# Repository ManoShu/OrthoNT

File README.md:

# OrthoNT

An open-source, QMK-compatible, (loosely) ABNT2-based 6x14 ortholinear keyboard.

---

Layout:

Links: [KLE](http://www.keyboard-layout-editor.com/#/gists/c8b4991d1be04ef7142aadfa52a7956e), [JSON](https://gist.github.com/ManoShu/c8b4991d1be04ef7142aadfa52a7956e), [QMK](https://github.com/ManoShu/OrthoNT/tree/main/qmk/keyboards/handwired/orthont)

---

## PCB & Plate
The gerber files are under `production`. They had been used and confirmed to work, however use them at your own risk.

## QMK

No plan to integrate to the main QMK repository yet, as I am waiting for a proper VID/PID allocation. The files are on the `qmk` directory; just copy folder to qmk and it should work (HOWEVER the files have been confirmed working on QMK 0.2.2 [check yours with `qmk --version`], previous versions might not have support for some of the tags in the` info.json` file).

## VIA / VIAL

**NOTE: VIA / VIAL files have not been uploaded yet**

A `via` keymap is available allowing to use VIA to change keybindings withou the need to setup QMK. 
It is not integrated with the official repository yet (as I am waiting for a proper VID allocation), but the .json file required to change bindings is available on the `via` directory.

A VIAL-compatible keymap is also available. Drop the keyboard folder to your `vial-qmk` directory and it should also work right off the bat.

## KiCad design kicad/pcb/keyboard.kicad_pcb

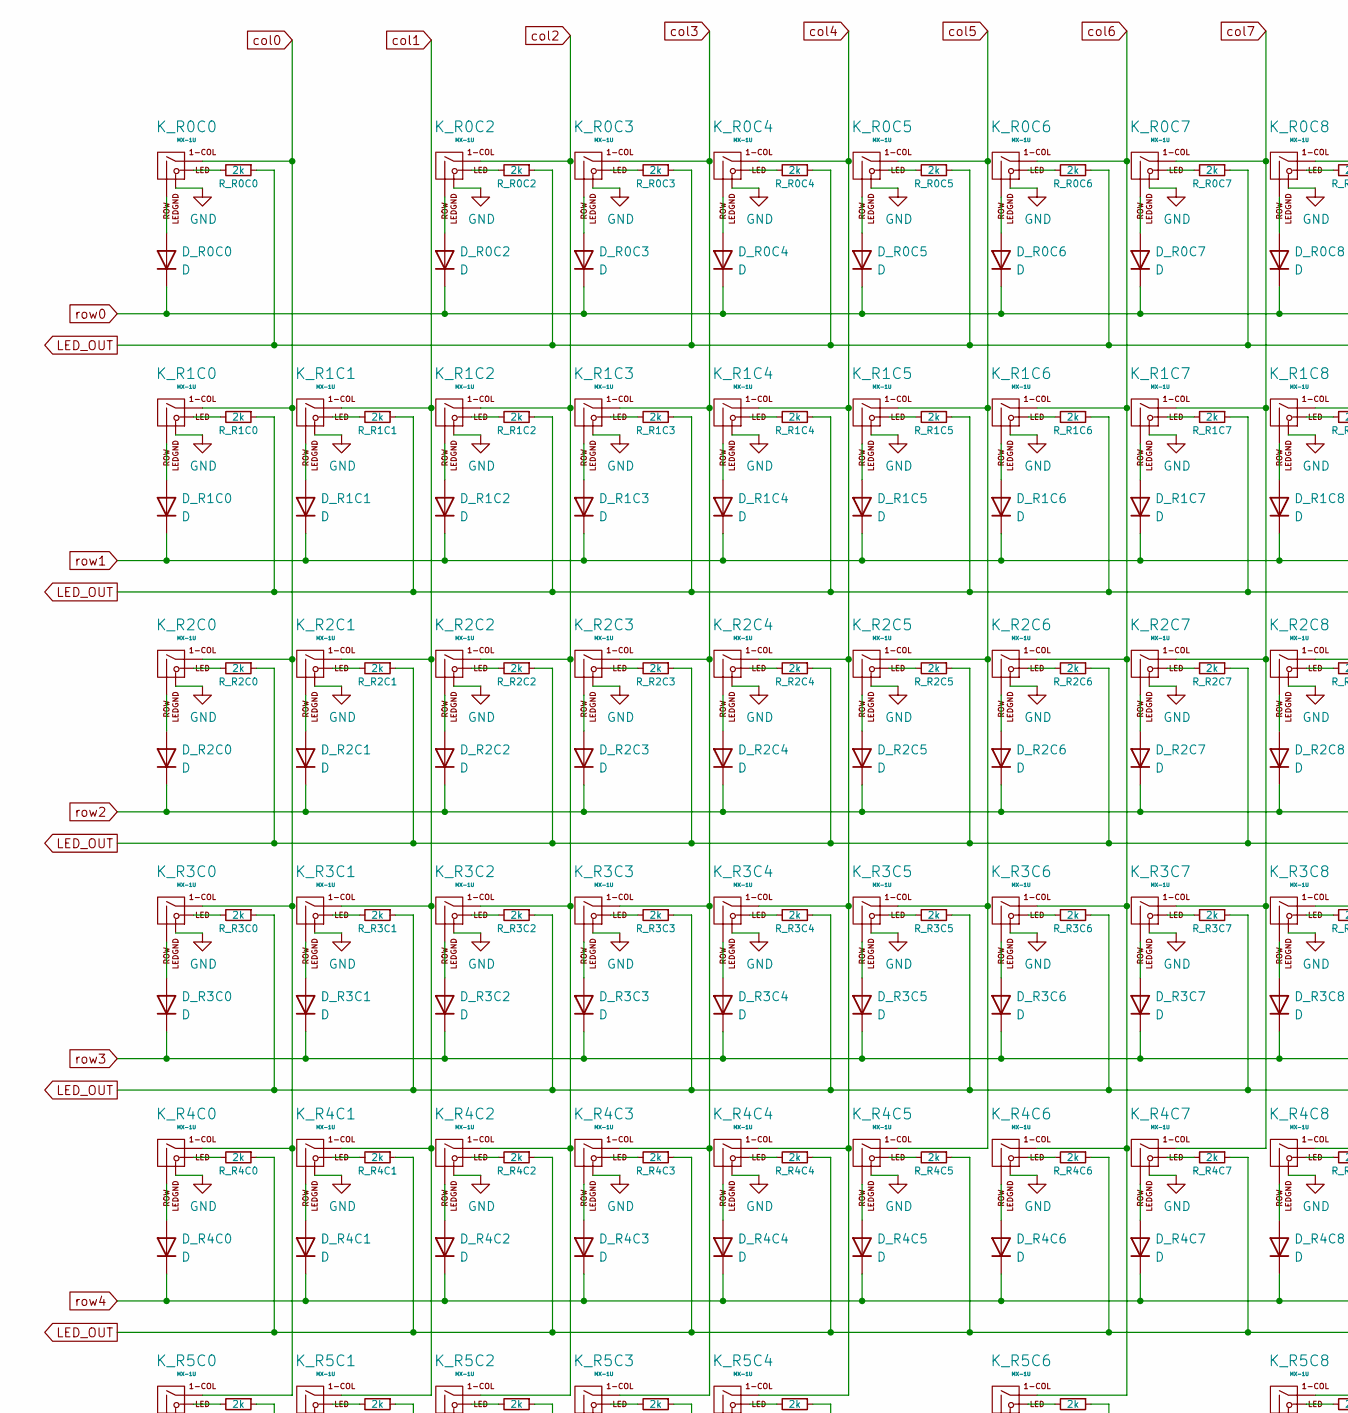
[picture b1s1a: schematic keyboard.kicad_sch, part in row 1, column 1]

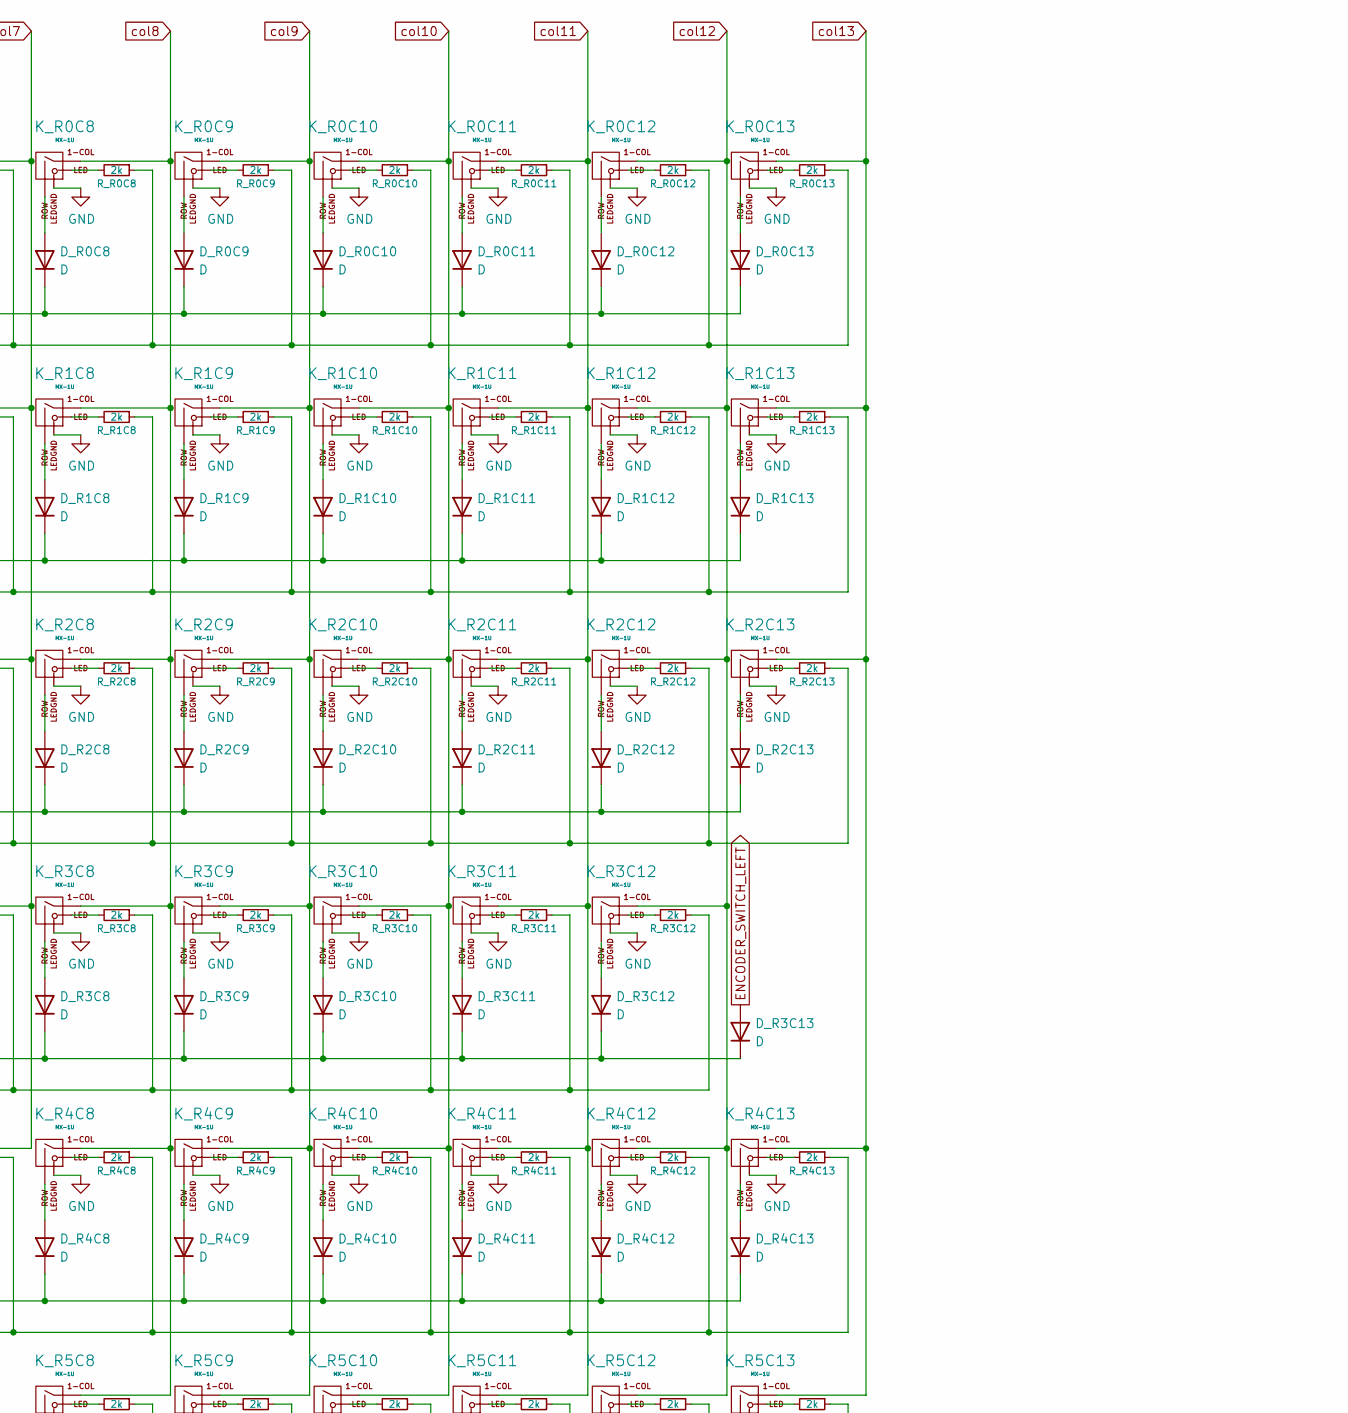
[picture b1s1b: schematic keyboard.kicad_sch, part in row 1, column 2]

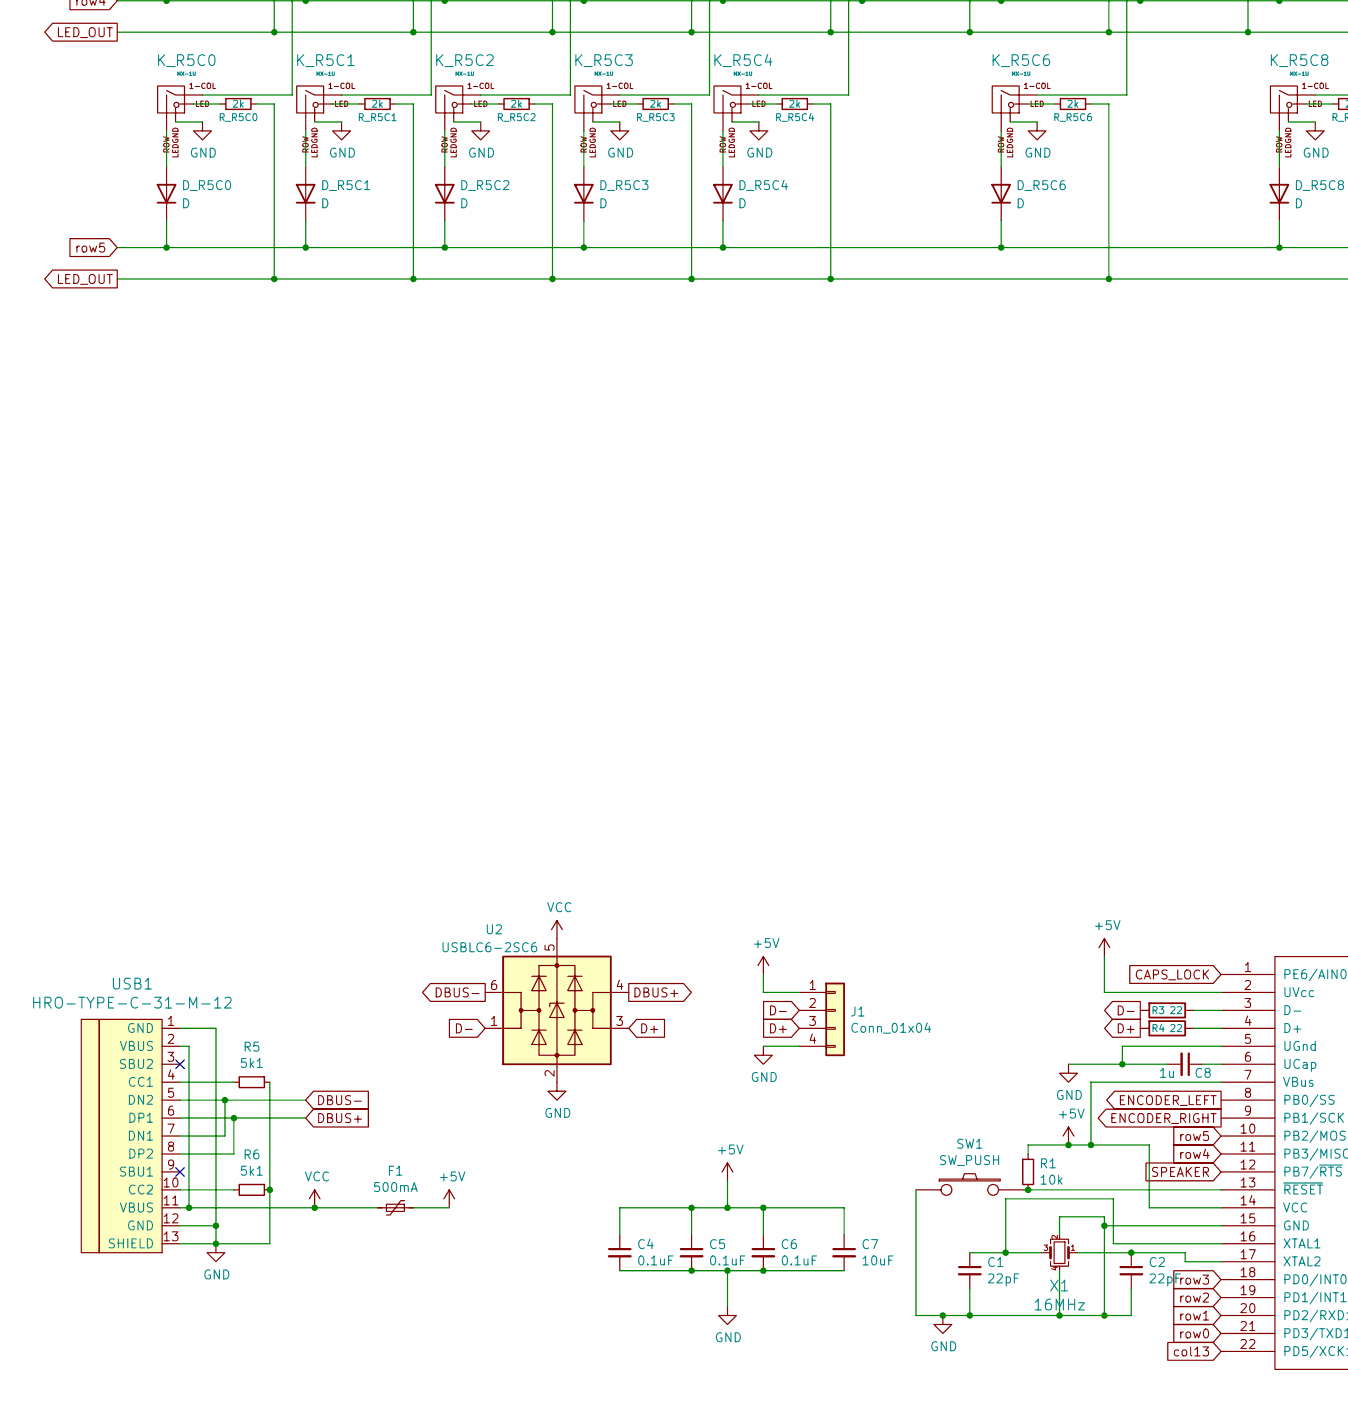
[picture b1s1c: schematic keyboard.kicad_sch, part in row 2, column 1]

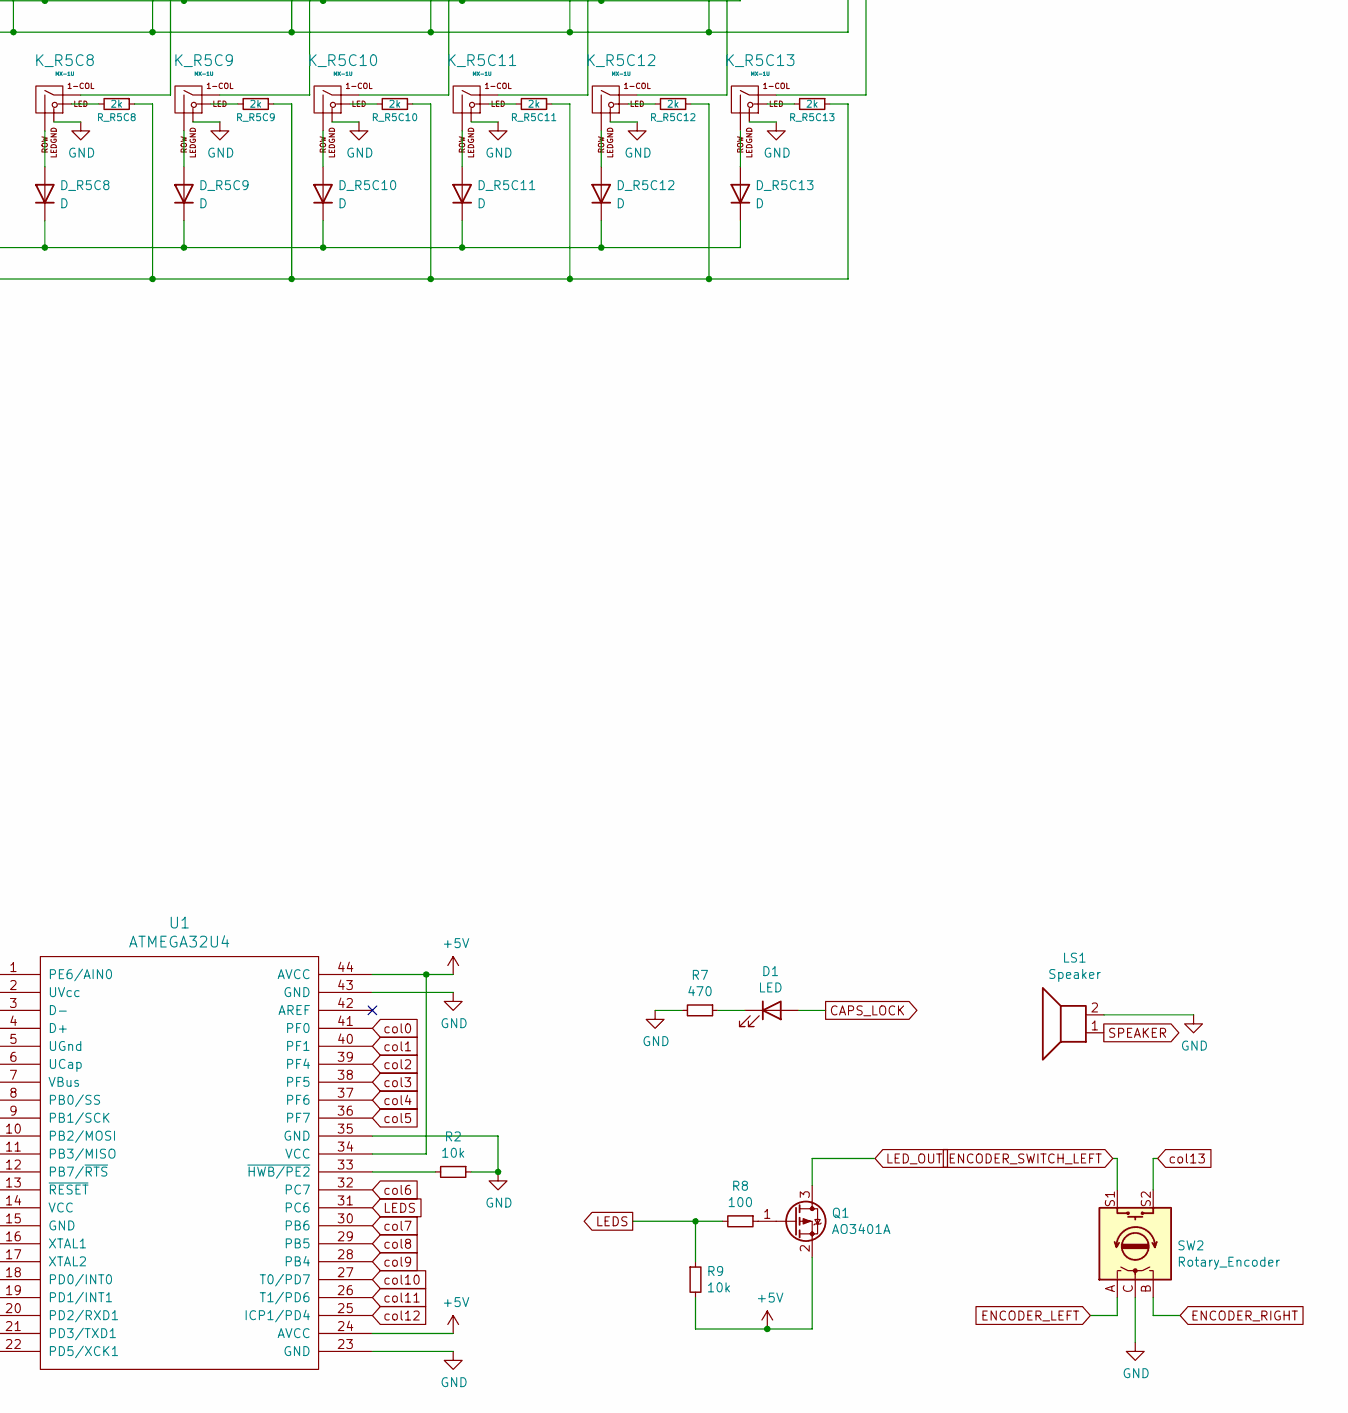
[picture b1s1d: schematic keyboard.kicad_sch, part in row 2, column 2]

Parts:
C1, C2: 22pF; C_0805_2012Metric_Pad1.15x1.40mm_HandSolder
C4, C5, C6: 0.1uF; C_0805_2012Metric_Pad1.15x1.40mm_HandSolder
C7: 10uF; C_0805_2012Metric_Pad1.15x1.40mm_HandSolder
C8: 1u; C_0805_2012Metric_Pad1.15x1.40mm_HandSolder
D1: LED; LED_0603_1608Metric_Pad1.05x0.95mm_HandSolder
D_R0C0, D_R0C2, D_R0C3, D_R0C4, D_R0C5, D_R0C6, D_R0C7, D_R0C8, D_R0C9, D_R0C10, D_R0C11, D_R0C12, D_R0C13, D_R1C0, D_R1C1, D_R1C2, D_R1C3, D_R1C4, D_R1C5, D_R1C6, D_R1C7, D_R1C8, D_R1C9, D_R1C10, D_R1C11, D_R1C12, D_R1C13, D_R2C0, D_R2C1, D_R2C2, D_R2C3, D_R2C4, D_R2C5, D_R2C6, D_R2C7, D_R2C8, D_R2C9, D_R2C10, D_R2C11, D_R2C12, D_R2C13, D_R3C0, D_R3C1, D_R3C2, D_R3C3, D_R3C4, D_R3C5, D_R3C6, D_R3C7, D_R3C8, D_R3C9, D_R3C10, D_R3C11, D_R3C12, D_R3C13, D_R4C0, D_R4C1, D_R4C2, D_R4C3, D_R4C4, D_R4C5, D_R4C6, D_R4C7, D_R4C8, D_R4C9, D_R4C10, D_R4C11, D_R4C12, D_R4C13, D_R5C0, D_R5C1, D_R5C2, D_R5C3, D_R5C4, D_R5C6, D_R5C8, D_R5C9, D_R5C10, D_R5C11, D_R5C12, D_R5C13: D; D_SOD123_hand
F1: 500mA; Fuse_1206_3216Metric_Pad1.42x1.75mm_HandSolder
J1: Conn_01x04; JST_SH_SM04B-SRSS-TB_1x04-1MP_P1.00mm_Horizontal
K_R0C0, K_R0C2, K_R0C3, K_R0C4, K_R0C5, K_R0C6, K_R0C7, K_R0C8, K_R0C9, K_R0C10, K_R0C11, K_R0C12, K_R0C13, K_R1C0, K_R1C1, K_R1C2, K_R1C3, K_R1C4, K_R1C5, K_R1C6, K_R1C7, K_R1C8, K_R1C9, K_R1C10, K_R1C11, K_R1C12, K_R1C13, K_R2C0, K_R2C1, K_R2C2, K_R2C3, K_R2C4, K_R2C5, K_R2C6, K_R2C7, K_R2C8, K_R2C9, K_R2C10, K_R2C11, K_R2C12, K_R3C0, K_R3C1, K_R3C2, K_R3C3, K_R3C4, K_R3C5, K_R3C6, K_R3C7, K_R3C8, K_R3C9, K_R3C10, K_R3C11, K_R3C12, K_R4C0, K_R4C1, K_R4C2, K_R4C3, K_R4C4, K_R4C5, K_R4C6, K_R4C7, K_R4C8, K_R4C9, K_R4C10, K_R4C11, K_R4C12, K_R4C13, K_R5C0, K_R5C1, K_R5C2, K_R5C3, K_R5C6, K_R5C9, K_R5C10, K_R5C11, K_R5C12, K_R5C13: MX-1U; MXOnly-1U
K_R2C13: MX-1U; MXOnly-2U_RightAngle
K_R5C4, K_R5C8: MX-1U; MXOnly-2U
LS1: Speaker; PinHeader_1x02_P2.54mm_Horizontal
Q1: AO3401A; SOT-23_Handsoldering
R1, R2, R9: 10k; R_0805_2012Metric_Pad1.15x1.40mm_HandSolder
R3, R4: 22; R_0805_2012Metric_Pad1.15x1.40mm_HandSolder
R5, R6: 5k1; R_0805_2012Metric_Pad1.15x1.40mm_HandSolder
R7: 470; R_0805_2012Metric_Pad1.15x1.40mm_HandSolder
R8: 100; R_0805_2012Metric_Pad1.15x1.40mm_HandSolder
R_R0C0, R_R0C2, R_R0C3, R_R0C4, R_R0C5, R_R0C6, R_R0C7, R_R0C8, R_R0C9, R_R0C10, R_R0C11, R_R0C12, R_R0C13, R_R1C0, R_R1C1, R_R1C2, R_R1C3, R_R1C4, R_R1C5, R_R1C6, R_R1C7, R_R1C8, R_R1C9, R_R1C10, R_R1C11, R_R1C12, R_R1C13, R_R2C0, R_R2C1, R_R2C2, R_R2C3, R_R2C4, R_R2C5, R_R2C6, R_R2C7, R_R2C8, R_R2C9, R_R2C10, R_R2C11, R_R2C12, R_R2C13, R_R3C0, R_R3C1, R_R3C2, R_R3C3, R_R3C4, R_R3C5, R_R3C6, R_R3C7, R_R3C8, R_R3C9, R_R3C10, R_R3C11, R_R3C12, R_R4C0, R_R4C1, R_R4C2, R_R4C3, R_R4C4, R_R4C5, R_R4C6, R_R4C7, R_R4C8, R_R4C9, R_R4C10, R_R4C11, R_R4C12, R_R4C13, R_R5C0, R_R5C1, R_R5C2, R_R5C3, R_R5C4, R_R5C6, R_R5C8, R_R5C9, R_R5C10, R_R5C11, R_R5C12, R_R5C13: 2k; R_0805_2012Metric_Pad1.15x1.40mm_HandSolder
SW1: SW_PUSH; SW_SPST_SKQG_WithStem
SW2: Rotary_Encoder; RotaryEncoder_Alps_EC11E-Switch_Vertical_H20mm
U1: ATMEGA32U4; TQFP-44_10x10mm_P0.8mm
U2: USBLC6-2SC6; SOT-23-6_Handsoldering
USB1: HRO-TYPE-C-31-M-12; HRO-TYPE-C-31-M-12-HandSoldering
X1: 16MHz; Crystal_SMD_3225-4Pin_3.2x2.5mm_HandSoldering

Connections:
+5V: C4.1, C5.1, C6.1, C7.1, F1.1, J1.1, Q1.2 (S), R1.1, R9.2, U1.2 (UVcc), U1.7 (VBus), U1.14 (VCC), U1.24 (AVCC), U1.34 (VCC), U1.44 (AVCC)
CAPS_LOCK: D1.2 (A), U1.1 (PE6/AIN0)
D+: J1.3, R4.2, U2.3 (I/O2)
D-: J1.2, R3.2, U2.1 (I/O1)
DBUS+: U2.4 (I/O2), USB1.6 (DP1), USB1.8 (DP2)
DBUS-: U2.6 (I/O1), USB1.5 (DN2), USB1.7 (DN1)
ENCODER_LEFT: SW2.A, U1.8 (PB0/SS)
ENCODER_RIGHT: SW2.B, U1.9 (PB1/SCK)
ENCODER_SWITCH_LEFT: D_R3C13.2 (A), SW2.S1
GND: C1.2, C2.2, C4.2, C5.2, C6.2, C7.2, C8.2, J1.4, K_R0C0.4 (LEDGND), K_R0C2.4 (LEDGND), K_R0C3.4 (LEDGND), K_R0C4.4 (LEDGND), K_R0C5.4 (LEDGND), K_R0C6.4 (LEDGND), K_R0C7.4 (LEDGND), K_R0C8.4 (LEDGND), K_R0C9.4 (LEDGND), K_R0C10.4 (LEDGND), K_R0C11.4 (LEDGND), K_R0C12.4 (LEDGND), K_R0C13.4 (LEDGND), K_R1C0.4 (LEDGND), K_R1C1.4 (LEDGND), K_R1C2.4 (LEDGND), K_R1C3.4 (LEDGND), K_R1C4.4 (LEDGND), K_R1C5.4 (LEDGND), K_R1C6.4 (LEDGND), K_R1C7.4 (LEDGND), K_R1C8.4 (LEDGND), K_R1C9.4 (LEDGND), K_R1C10.4 (LEDGND), K_R1C11.4 (LEDGND), K_R1C12.4 (LEDGND), K_R1C13.4 (LEDGND), K_R2C0.4 (LEDGND), K_R2C1.4 (LEDGND), K_R2C2.4 (LEDGND), K_R2C3.4 (LEDGND), K_R2C4.4 (LEDGND), K_R2C5.4 (LEDGND), K_R2C6.4 (LEDGND), K_R2C7.4 (LEDGND), K_R2C8.4 (LEDGND), K_R2C9.4 (LEDGND), K_R2C10.4 (LEDGND), K_R2C11.4 (LEDGND), K_R2C12.4 (LEDGND), K_R2C13.4 (LEDGND), K_R3C0.4 (LEDGND), K_R3C1.4 (LEDGND), K_R3C2.4 (LEDGND), K_R3C3.4 (LEDGND), K_R3C4.4 (LEDGND), K_R3C5.4 (LEDGND), K_R3C6.4 (LEDGND), K_R3C7.4 (LEDGND), K_R3C8.4 (LEDGND), K_R3C9.4 (LEDGND), K_R3C10.4 (LEDGND), K_R3C11.4 (LEDGND), K_R3C12.4 (LEDGND), K_R4C0.4 (LEDGND), K_R4C1.4 (LEDGND), K_R4C2.4 (LEDGND), K_R4C3.4 (LEDGND), K_R4C4.4 (LEDGND), K_R4C5.4 (LEDGND), K_R4C6.4 (LEDGND), K_R4C7.4 (LEDGND), K_R4C8.4 (LEDGND), K_R4C9.4 (LEDGND), K_R4C10.4 (LEDGND), K_R4C11.4 (LEDGND), K_R4C12.4 (LEDGND), K_R4C13.4 (LEDGND), K_R5C0.4 (LEDGND), K_R5C1.4 (LEDGND), K_R5C2.4 (LEDGND), K_R5C3.4 (LEDGND), K_R5C4.4 (LEDGND), K_R5C6.4 (LEDGND), K_R5C8.4 (LEDGND), K_R5C9.4 (LEDGND), K_R5C10.4 (LEDGND), K_R5C11.4 (LEDGND), K_R5C12.4 (LEDGND), K_R5C13.4 (LEDGND), LS1.2, R2.1, R5.1, R6.1, R7.2, SW1.1, SW2.C, U1.5 (UGnd), U1.15 (GND), U1.23 (GND), U1.35 (GND), U1.43 (GND), U2.2 (GND), USB1.1 (GND), USB1.12 (GND), USB1.13 (SHIELD), X1.2, X1.4
LEDS: R8.2, R9.1, U1.31 (PC6)
LED_OUT: Q1.3 (D), R_R0C0.1, R_R0C2.1, R_R0C3.1, R_R0C4.1, R_R0C5.1, R_R0C6.1, R_R0C7.1, R_R0C8.1, R_R0C9.1, R_R0C10.1, R_R0C11.1, R_R0C12.1, R_R0C13.1, R_R1C0.1, R_R1C1.1, R_R1C2.1, R_R1C3.1, R_R1C4.1, R_R1C5.1, R_R1C6.1, R_R1C7.1, R_R1C8.1, R_R1C9.1, R_R1C10.1, R_R1C11.1, R_R1C12.1, R_R1C13.1, R_R2C0.1, R_R2C1.1, R_R2C2.1, R_R2C3.1, R_R2C4.1, R_R2C5.1, R_R2C6.1, R_R2C7.1, R_R2C8.1, R_R2C9.1, R_R2C10.1, R_R2C11.1, R_R2C12.1, R_R2C13.1, R_R3C0.1, R_R3C1.1, R_R3C2.1, R_R3C3.1, R_R3C4.1, R_R3C5.1, R_R3C6.1, R_R3C7.1, R_R3C8.1, R_R3C9.1, R_R3C10.1, R_R3C11.1, R_R3C12.1, R_R4C0.1, R_R4C1.1, R_R4C2.1, R_R4C3.1, R_R4C4.1, R_R4C5.1, R_R4C6.1, R_R4C7.1, R_R4C8.1, R_R4C9.1, R_R4C10.1, R_R4C11.1, R_R4C12.1, R_R4C13.1, R_R5C0.1, R_R5C1.1, R_R5C2.1, R_R5C3.1, R_R5C4.1, R_R5C6.1, R_R5C8.1, R_R5C9.1, R_R5C10.1, R_R5C11.1, R_R5C12.1, R_R5C13.1
unnamed: C1.1, U1.16 (XTAL1), X1.3
unnamed: C2.1, U1.17 (XTAL2), X1.1
unnamed: C8.1, U1.6 (UCap)
unnamed: D1.1 (K), R7.1
unnamed: D_R0C0.2 (A), K_R0C0.2 (ROW)
unnamed: D_R0C2.2 (A), K_R0C2.2 (ROW)
unnamed: D_R0C3.2 (A), K_R0C3.2 (ROW)
unnamed: D_R0C4.2 (A), K_R0C4.2 (ROW)
unnamed: D_R0C5.2 (A), K_R0C5.2 (ROW)
unnamed: D_R0C6.2 (A), K_R0C6.2 (ROW)
unnamed: D_R0C7.2 (A), K_R0C7.2 (ROW)
unnamed: D_R0C8.2 (A), K_R0C8.2 (ROW)
unnamed: D_R0C9.2 (A), K_R0C9.2 (ROW)
unnamed: D_R0C10.2 (A), K_R0C10.2 (ROW)
unnamed: D_R0C11.2 (A), K_R0C11.2 (ROW)
unnamed: D_R0C12.2 (A), K_R0C12.2 (ROW)
unnamed: D_R0C13.2 (A), K_R0C13.2 (ROW)
unnamed: D_R1C0.2 (A), K_R1C0.2 (ROW)
unnamed: D_R1C1.2 (A), K_R1C1.2 (ROW)
unnamed: D_R1C2.2 (A), K_R1C2.2 (ROW)
unnamed: D_R1C3.2 (A), K_R1C3.2 (ROW)
unnamed: D_R1C4.2 (A), K_R1C4.2 (ROW)
unnamed: D_R1C5.2 (A), K_R1C5.2 (ROW)
unnamed: D_R1C6.2 (A), K_R1C6.2 (ROW)
unnamed: D_R1C7.2 (A), K_R1C7.2 (ROW)
unnamed: D_R1C8.2 (A), K_R1C8.2 (ROW)
unnamed: D_R1C9.2 (A), K_R1C9.2 (ROW)
unnamed: D_R1C10.2 (A), K_R1C10.2 (ROW)
unnamed: D_R1C11.2 (A), K_R1C11.2 (ROW)
unnamed: D_R1C12.2 (A), K_R1C12.2 (ROW)
unnamed: D_R1C13.2 (A), K_R1C13.2 (ROW)
unnamed: D_R2C0.2 (A), K_R2C0.2 (ROW)
unnamed: D_R2C1.2 (A), K_R2C1.2 (ROW)
unnamed: D_R2C2.2 (A), K_R2C2.2 (ROW)
unnamed: D_R2C3.2 (A), K_R2C3.2 (ROW)
unnamed: D_R2C4.2 (A), K_R2C4.2 (ROW)
unnamed: D_R2C5.2 (A), K_R2C5.2 (ROW)
unnamed: D_R2C6.2 (A), K_R2C6.2 (ROW)
unnamed: D_R2C7.2 (A), K_R2C7.2 (ROW)
unnamed: D_R2C8.2 (A), K_R2C8.2 (ROW)
unnamed: D_R2C9.2 (A), K_R2C9.2 (ROW)
unnamed: D_R2C10.2 (A), K_R2C10.2 (ROW)
unnamed: D_R2C11.2 (A), K_R2C11.2 (ROW)
unnamed: D_R2C12.2 (A), K_R2C12.2 (ROW)
unnamed: D_R2C13.2 (A), K_R2C13.2 (ROW)
unnamed: D_R3C0.2 (A), K_R3C0.2 (ROW)
unnamed: D_R3C1.2 (A), K_R3C1.2 (ROW)
unnamed: D_R3C2.2 (A), K_R3C2.2 (ROW)
unnamed: D_R3C3.2 (A), K_R3C3.2 (ROW)
unnamed: D_R3C4.2 (A), K_R3C4.2 (ROW)
unnamed: D_R3C5.2 (A), K_R3C5.2 (ROW)
unnamed: D_R3C6.2 (A), K_R3C6.2 (ROW)
unnamed: D_R3C7.2 (A), K_R3C7.2 (ROW)
unnamed: D_R3C8.2 (A), K_R3C8.2 (ROW)
unnamed: D_R3C9.2 (A), K_R3C9.2 (ROW)
unnamed: D_R3C10.2 (A), K_R3C10.2 (ROW)
unnamed: D_R3C11.2 (A), K_R3C11.2 (ROW)
unnamed: D_R3C12.2 (A), K_R3C12.2 (ROW)
unnamed: D_R4C0.2 (A), K_R4C0.2 (ROW)
unnamed: D_R4C1.2 (A), K_R4C1.2 (ROW)
unnamed: D_R4C2.2 (A), K_R4C2.2 (ROW)
unnamed: D_R4C3.2 (A), K_R4C3.2 (ROW)
unnamed: D_R4C4.2 (A), K_R4C4.2 (ROW)
unnamed: D_R4C5.2 (A), K_R4C5.2 (ROW)
unnamed: D_R4C6.2 (A), K_R4C6.2 (ROW)
unnamed: D_R4C7.2 (A), K_R4C7.2 (ROW)
unnamed: D_R4C8.2 (A), K_R4C8.2 (ROW)
unnamed: D_R4C9.2 (A), K_R4C9.2 (ROW)
unnamed: D_R4C10.2 (A), K_R4C10.2 (ROW)
unnamed: D_R4C11.2 (A), K_R4C11.2 (ROW)
unnamed: D_R4C12.2 (A), K_R4C12.2 (ROW)
unnamed: D_R4C13.2 (A), K_R4C13.2 (ROW)
unnamed: D_R5C0.2 (A), K_R5C0.2 (ROW)
unnamed: D_R5C1.2 (A), K_R5C1.2 (ROW)
unnamed: D_R5C2.2 (A), K_R5C2.2 (ROW)
unnamed: D_R5C3.2 (A), K_R5C3.2 (ROW)
unnamed: D_R5C4.2 (A), K_R5C4.2 (ROW)
unnamed: D_R5C6.2 (A), K_R5C6.2 (ROW)
unnamed: D_R5C8.2 (A), K_R5C8.2 (ROW)
unnamed: D_R5C9.2 (A), K_R5C9.2 (ROW)
unnamed: D_R5C10.2 (A), K_R5C10.2 (ROW)
unnamed: D_R5C11.2 (A), K_R5C11.2 (ROW)
unnamed: D_R5C12.2 (A), K_R5C12.2 (ROW)
unnamed: D_R5C13.2 (A), K_R5C13.2 (ROW)
unnamed: K_R0C0.3 (LED), R_R0C0.2
unnamed: K_R0C2.3 (LED), R_R0C2.2
unnamed: K_R0C3.3 (LED), R_R0C3.2
unnamed: K_R0C4.3 (LED), R_R0C4.2
unnamed: K_R0C5.3 (LED), R_R0C5.2
unnamed: K_R0C6.3 (LED), R_R0C6.2
unnamed: K_R0C7.3 (LED), R_R0C7.2
unnamed: K_R0C8.3 (LED), R_R0C8.2
unnamed: K_R0C9.3 (LED), R_R0C9.2
unnamed: K_R0C10.3 (LED), R_R0C10.2
unnamed: K_R0C11.3 (LED), R_R0C11.2
unnamed: K_R0C12.3 (LED), R_R0C12.2
unnamed: K_R0C13.3 (LED), R_R0C13.2
unnamed: K_R1C0.3 (LED), R_R1C0.2
unnamed: K_R1C1.3 (LED), R_R1C1.2
unnamed: K_R1C2.3 (LED), R_R1C2.2
unnamed: K_R1C3.3 (LED), R_R1C3.2
unnamed: K_R1C4.3 (LED), R_R1C4.2
unnamed: K_R1C5.3 (LED), R_R1C5.2
unnamed: K_R1C6.3 (LED), R_R1C6.2
unnamed: K_R1C7.3 (LED), R_R1C7.2
unnamed: K_R1C8.3 (LED), R_R1C8.2
unnamed: K_R1C9.3 (LED), R_R1C9.2
unnamed: K_R1C10.3 (LED), R_R1C10.2
unnamed: K_R1C11.3 (LED), R_R1C11.2
unnamed: K_R1C12.3 (LED), R_R1C12.2
unnamed: K_R1C13.3 (LED), R_R1C13.2
unnamed: K_R2C0.3 (LED), R_R2C0.2
unnamed: K_R2C1.3 (LED), R_R2C1.2
unnamed: K_R2C2.3 (LED), R_R2C2.2
unnamed: K_R2C3.3 (LED), R_R2C3.2
unnamed: K_R2C4.3 (LED), R_R2C4.2
unnamed: K_R2C5.3 (LED), R_R2C5.2
unnamed: K_R2C6.3 (LED), R_R2C6.2
unnamed: K_R2C7.3 (LED), R_R2C7.2
unnamed: K_R2C8.3 (LED), R_R2C8.2
unnamed: K_R2C9.3 (LED), R_R2C9.2
unnamed: K_R2C10.3 (LED), R_R2C10.2
unnamed: K_R2C11.3 (LED), R_R2C11.2
unnamed: K_R2C12.3 (LED), R_R2C12.2
unnamed: K_R2C13.3 (LED), R_R2C13.2
unnamed: K_R3C0.3 (LED), R_R3C0.2
unnamed: K_R3C1.3 (LED), R_R3C1.2
unnamed: K_R3C2.3 (LED), R_R3C2.2
unnamed: K_R3C3.3 (LED), R_R3C3.2
unnamed: K_R3C4.3 (LED), R_R3C4.2
unnamed: K_R3C5.3 (LED), R_R3C5.2
unnamed: K_R3C6.3 (LED), R_R3C6.2
unnamed: K_R3C7.3 (LED), R_R3C7.2
unnamed: K_R3C8.3 (LED), R_R3C8.2
unnamed: K_R3C9.3 (LED), R_R3C9.2
unnamed: K_R3C10.3 (LED), R_R3C10.2
unnamed: K_R3C11.3 (LED), R_R3C11.2
unnamed: K_R3C12.3 (LED), R_R3C12.2
unnamed: K_R4C0.3 (LED), R_R4C0.2
unnamed: K_R4C1.3 (LED), R_R4C1.2
unnamed: K_R4C2.3 (LED), R_R4C2.2
unnamed: K_R4C3.3 (LED), R_R4C3.2
unnamed: K_R4C4.3 (LED), R_R4C4.2
unnamed: K_R4C5.3 (LED), R_R4C5.2
unnamed: K_R4C6.3 (LED), R_R4C6.2
unnamed: K_R4C7.3 (LED), R_R4C7.2
unnamed: K_R4C8.3 (LED), R_R4C8.2
unnamed: K_R4C9.3 (LED), R_R4C9.2
unnamed: K_R4C10.3 (LED), R_R4C10.2
unnamed: K_R4C11.3 (LED), R_R4C11.2
unnamed: K_R4C12.3 (LED), R_R4C12.2
unnamed: K_R4C13.3 (LED), R_R4C13.2
unnamed: K_R5C0.3 (LED), R_R5C0.2
unnamed: K_R5C1.3 (LED), R_R5C1.2
unnamed: K_R5C2.3 (LED), R_R5C2.2
unnamed: K_R5C3.3 (LED), R_R5C3.2
unnamed: K_R5C4.3 (LED), R_R5C4.2
unnamed: K_R5C6.3 (LED), R_R5C6.2
unnamed: K_R5C8.3 (LED), R_R5C8.2
unnamed: K_R5C9.3 (LED), R_R5C9.2
unnamed: K_R5C10.3 (LED), R_R5C10.2
unnamed: K_R5C11.3 (LED), R_R5C11.2
unnamed: K_R5C12.3 (LED), R_R5C12.2
unnamed: K_R5C13.3 (LED), R_R5C13.2
unnamed: Q1.1 (G), R8.1
unnamed: R1.2, SW1.2, U1.13 (~RESET)
unnamed: R2.2, U1.33 (~HWB/PE2)
unnamed: R3.1, U1.3 (D-)
unnamed: R4.1, U1.4 (D+)
unnamed: R5.2, USB1.4 (CC1)
unnamed: R6.2, USB1.10 (CC2)
SPEAKER: LS1.1, U1.12 (PB7/~RTS)
VCC: F1.2, U2.5 (VBUS), USB1.2 (VBUS), USB1.11 (VBUS)
col0: K_R0C0.1 (COL), K_R1C0.1 (COL), K_R2C0.1 (COL), K_R3C0.1 (COL), K_R4C0.1 (COL), K_R5C0.1 (COL), U1.41 (PF0)
col1: K_R1C1.1 (COL), K_R2C1.1 (COL), K_R3C1.1 (COL), K_R4C1.1 (COL), K_R5C1.1 (COL), U1.40 (PF1)
col2: K_R0C2.1 (COL), K_R1C2.1 (COL), K_R2C2.1 (COL), K_R3C2.1 (COL), K_R4C2.1 (COL), K_R5C2.1 (COL), U1.39 (PF4)
col3: K_R0C3.1 (COL), K_R1C3.1 (COL), K_R2C3.1 (COL), K_R3C3.1 (COL), K_R4C3.1 (COL), K_R5C3.1 (COL), U1.38 (PF5)
col4: K_R0C4.1 (COL), K_R1C4.1 (COL), K_R2C4.1 (COL), K_R3C4.1 (COL), K_R4C4.1 (COL), K_R5C4.1 (COL), U1.37 (PF6)
col5: K_R0C5.1 (COL), K_R1C5.1 (COL), K_R2C5.1 (COL), K_R3C5.1 (COL), K_R4C5.1 (COL), U1.36 (PF7)
col6: K_R0C6.1 (COL), K_R1C6.1 (COL), K_R2C6.1 (COL), K_R3C6.1 (COL), K_R4C6.1 (COL), K_R5C6.1 (COL), U1.32 (PC7)
col7: K_R0C7.1 (COL), K_R1C7.1 (COL), K_R2C7.1 (COL), K_R3C7.1 (COL), K_R4C7.1 (COL), U1.30 (PB6)
col8: K_R0C8.1 (COL), K_R1C8.1 (COL), K_R2C8.1 (COL), K_R3C8.1 (COL), K_R4C8.1 (COL), K_R5C8.1 (COL), U1.29 (PB5)
col9: K_R0C9.1 (COL), K_R1C9.1 (COL), K_R2C9.1 (COL), K_R3C9.1 (COL), K_R4C9.1 (COL), K_R5C9.1 (COL), U1.28 (PB4)
col10: K_R0C10.1 (COL), K_R1C10.1 (COL), K_R2C10.1 (COL), K_R3C10.1 (COL), K_R4C10.1 (COL), K_R5C10.1 (COL), U1.27 (T0/PD7)
col11: K_R0C11.1 (COL), K_R1C11.1 (COL), K_R2C11.1 (COL), K_R3C11.1 (COL), K_R4C11.1 (COL), K_R5C11.1 (COL), U1.26 (T1/PD6)
col12: K_R0C12.1 (COL), K_R1C12.1 (COL), K_R2C12.1 (COL), K_R3C12.1 (COL), K_R4C12.1 (COL), K_R5C12.1 (COL), U1.25 (ICP1/PD4)
col13: K_R0C13.1 (COL), K_R1C13.1 (COL), K_R2C13.1 (COL), K_R4C13.1 (COL), K_R5C13.1 (COL), SW2.S2, U1.22 (PD5/XCK1)
row0: D_R0C0.1 (K), D_R0C2.1 (K), D_R0C3.1 (K), D_R0C4.1 (K), D_R0C5.1 (K), D_R0C6.1 (K), D_R0C7.1 (K), D_R0C8.1 (K), D_R0C9.1 (K), D_R0C10.1 (K), D_R0C11.1 (K), D_R0C12.1 (K), D_R0C13.1 (K), U1.21 (PD3/TXD1)
row1: D_R1C0.1 (K), D_R1C1.1 (K), D_R1C2.1 (K), D_R1C3.1 (K), D_R1C4.1 (K), D_R1C5.1 (K), D_R1C6.1 (K), D_R1C7.1 (K), D_R1C8.1 (K), D_R1C9.1 (K), D_R1C10.1 (K), D_R1C11.1 (K), D_R1C12.1 (K), D_R1C13.1 (K), U1.20 (PD2/RXD1)
row2: D_R2C0.1 (K), D_R2C1.1 (K), D_R2C2.1 (K), D_R2C3.1 (K), D_R2C4.1 (K), D_R2C5.1 (K), D_R2C6.1 (K), D_R2C7.1 (K), D_R2C8.1 (K), D_R2C9.1 (K), D_R2C10.1 (K), D_R2C11.1 (K), D_R2C12.1 (K), D_R2C13.1 (K), U1.19 (PD1/INT1)
row3: D_R3C0.1 (K), D_R3C1.1 (K), D_R3C2.1 (K), D_R3C3.1 (K), D_R3C4.1 (K), D_R3C5.1 (K), D_R3C6.1 (K), D_R3C7.1 (K), D_R3C8.1 (K), D_R3C9.1 (K), D_R3C10.1 (K), D_R3C11.1 (K), D_R3C12.1 (K), D_R3C13.1 (K), U1.18 (PD0/INT0)
row4: D_R4C0.1 (K), D_R4C1.1 (K), D_R4C2.1 (K), D_R4C3.1 (K), D_R4C4.1 (K), D_R4C5.1 (K), D_R4C6.1 (K), D_R4C7.1 (K), D_R4C8.1 (K), D_R4C9.1 (K), D_R4C10.1 (K), D_R4C11.1 (K), D_R4C12.1 (K), D_R4C13.1 (K), U1.11 (PB3/MISO)
row5: D_R5C0.1 (K), D_R5C1.1 (K), D_R5C2.1 (K), D_R5C3.1 (K), D_R5C4.1 (K), D_R5C6.1 (K), D_R5C8.1 (K), D_R5C9.1 (K), D_R5C10.1 (K), D_R5C11.1 (K), D_R5C12.1 (K), D_R5C13.1 (K), U1.10 (PB2/MOSI)

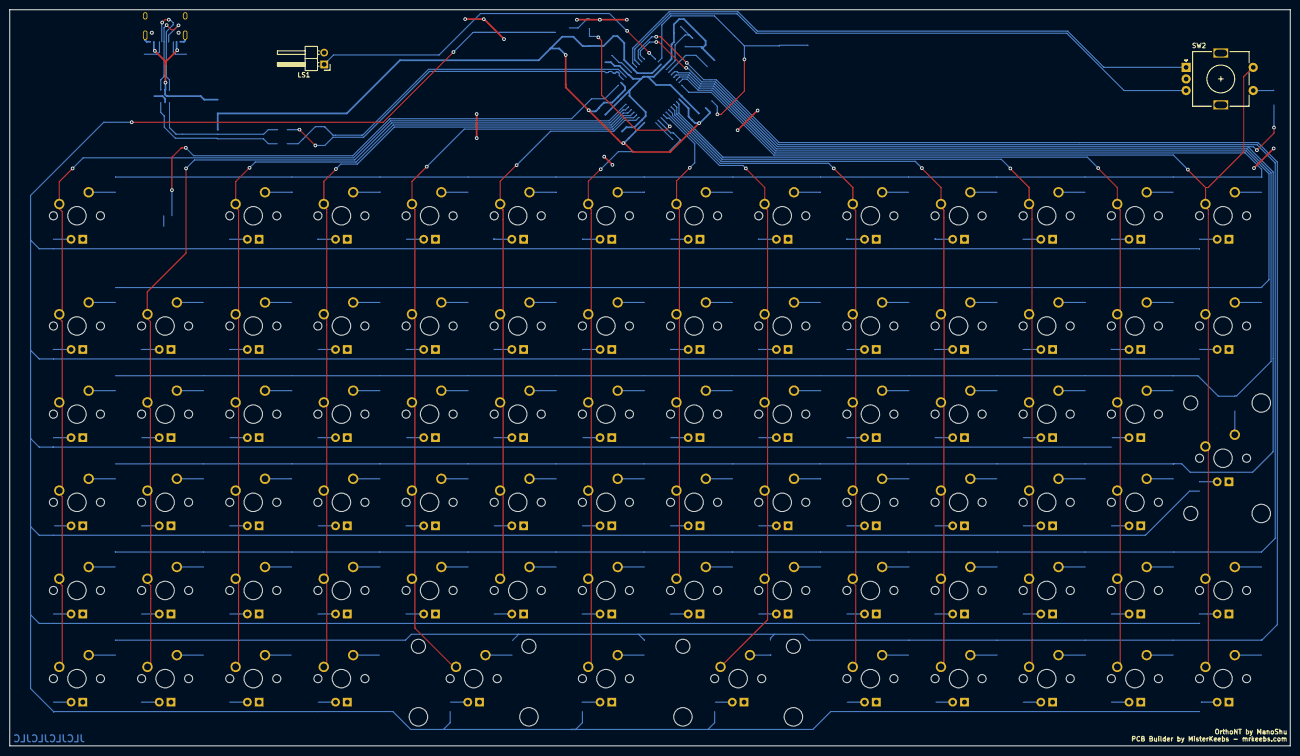
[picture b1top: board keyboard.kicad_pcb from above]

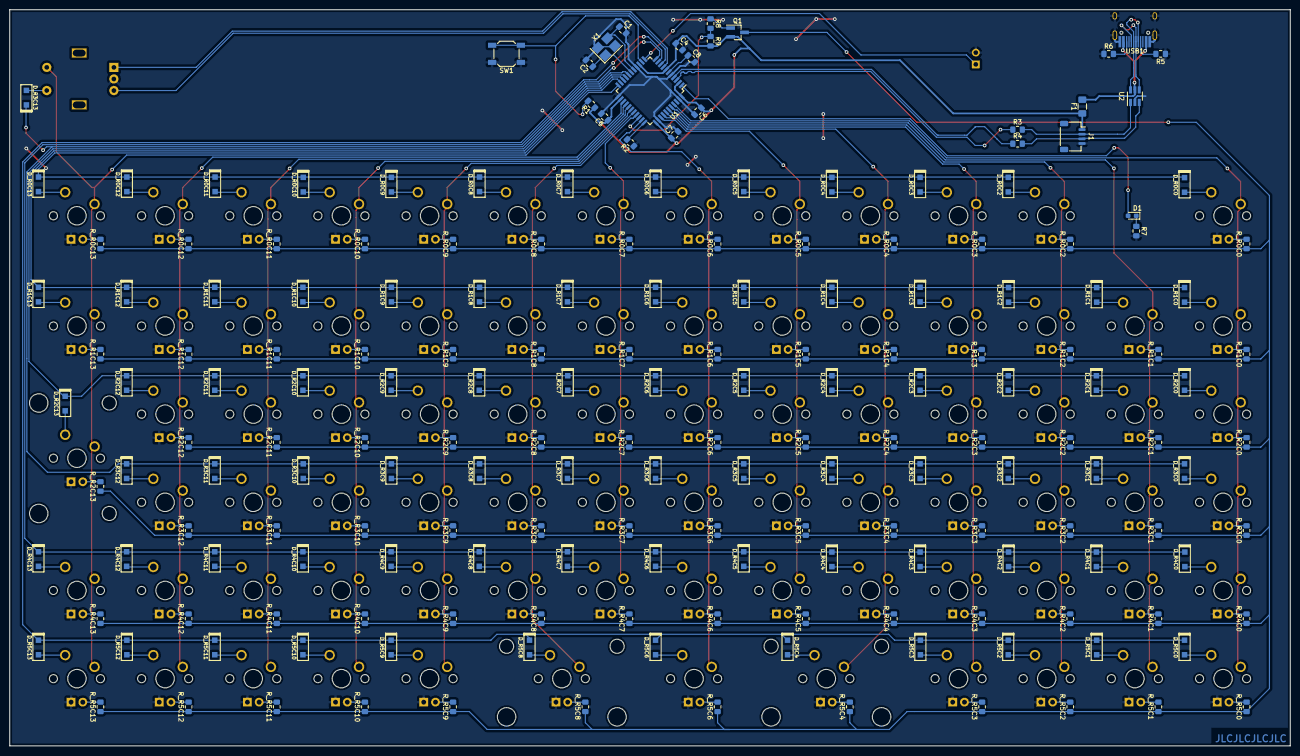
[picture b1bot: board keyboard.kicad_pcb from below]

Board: 2 copper layers, 276.7 x 159.1 mm, 268 parts (186 on the bottom side), 205 nets.

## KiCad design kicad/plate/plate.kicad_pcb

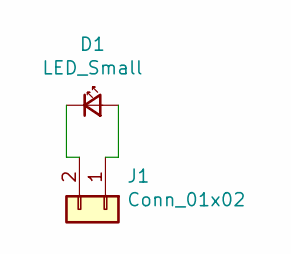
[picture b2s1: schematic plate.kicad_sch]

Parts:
D1: LED_Small; LED_1206_3216Metric_ReverseMount_Hole1.8x2.4mm
J1: Conn_01x02; LED_2816_7142Metric_Pad3.20x4.45mm_HandSolder

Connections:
unnamed: D1.1 (K), J1.2
unnamed: D1.2 (A), J1.1

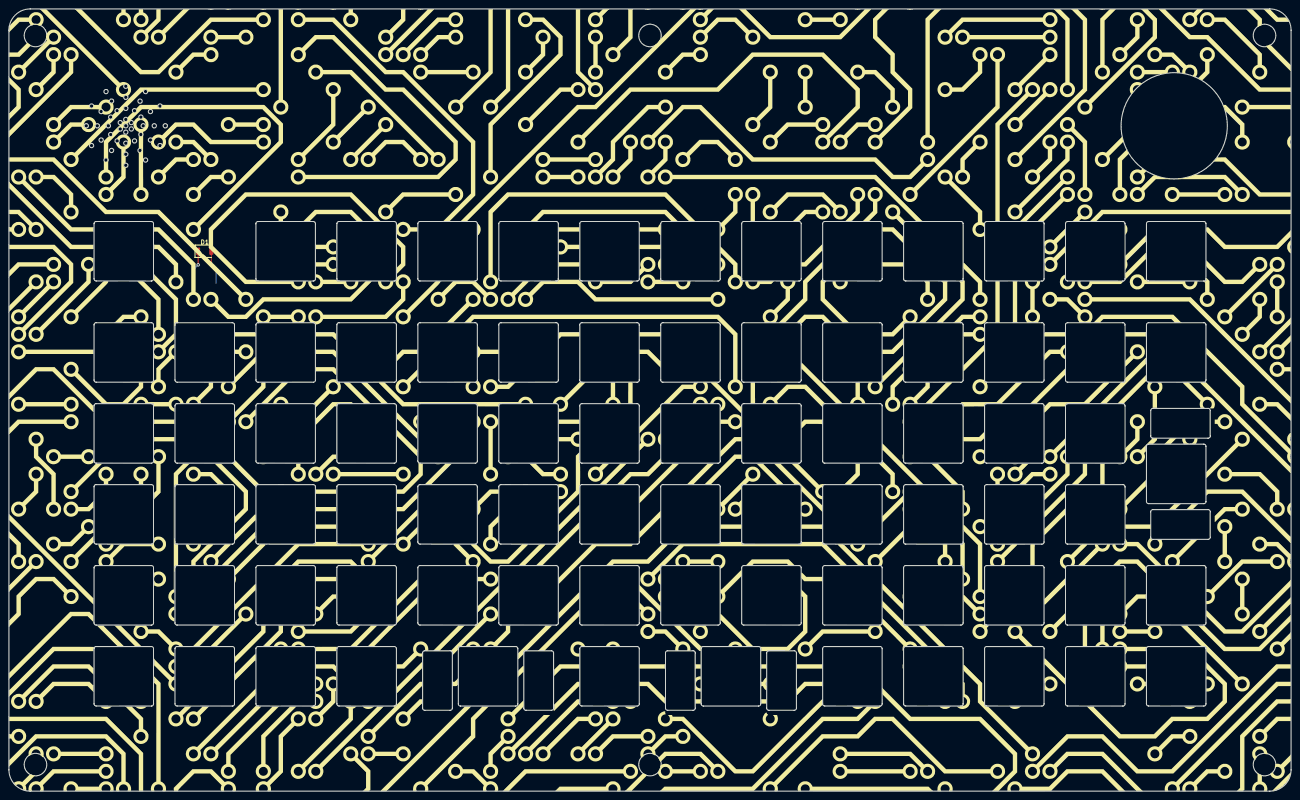
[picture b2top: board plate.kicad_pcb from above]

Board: 2 copper layers, 301.7 x 184.1 mm, 3 parts (1 on the bottom side), 2 nets.

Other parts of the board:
.: .; Hole_25mm

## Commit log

2022-02-04 Main files upload
2022-02-04 Disabling submodule tracking
2022-02-04 Fixed backlight levels and pin definition for caps lock
2022-02-04 Added initial README
